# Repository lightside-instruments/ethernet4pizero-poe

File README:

The ethernet4pizero-poe project is open hardware design of a Raspbery Pi
shield that adds Ethernet over SPI connectivity with the ENC28J60 IC and
Power over Ethernet (POE) capability that can supply 2A at 5V.

The powermod directory contains design of a submodule board to handle DC-DC
conversion. The powermod submodule interface is generic and the
implementation added is based on tps54260. 

The project includes schematics and PCB
design files for KiCAD. The board can be used with
the dtoverlay=enc28j60 option added to /boot/config.txt.

The project is published by Lightside Instruments AS
under TAPR Open Hardware License. Read the LICENSE file
for details.

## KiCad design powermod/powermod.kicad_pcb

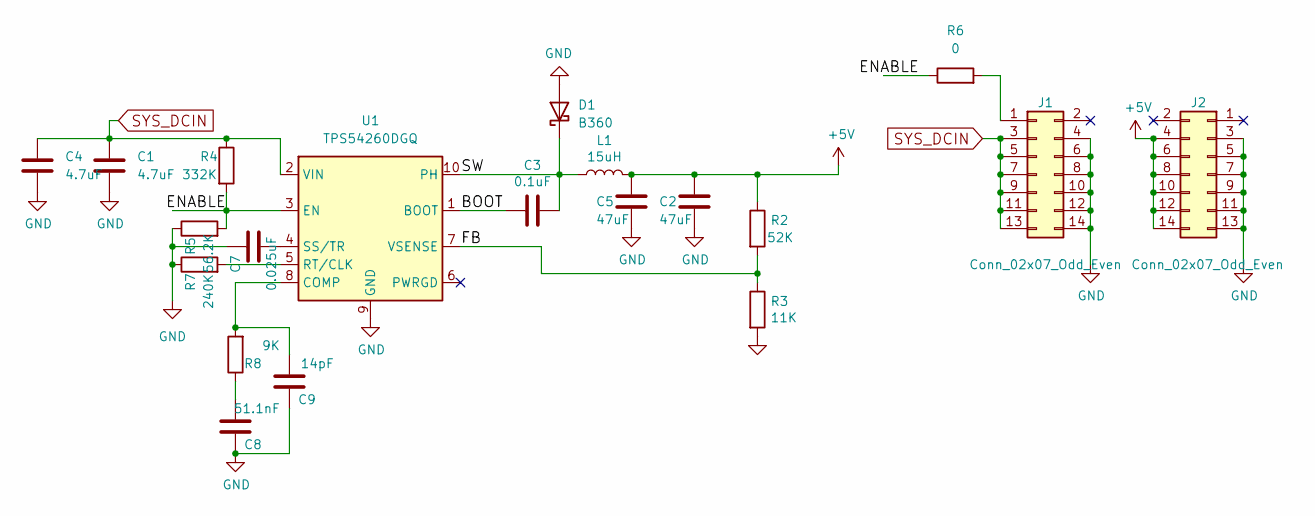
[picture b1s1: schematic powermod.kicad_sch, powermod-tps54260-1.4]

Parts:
C1, C4: 4.7uF; C_1210_3225Metric
C2, C5: 47uF; C_0805_2012Metric
C3: 0.1uF; C_0402_1005Metric
C7: 0.025uF; C_0402_1005Metric
C8: 51.1nF; C_0402_1005Metric
C9: 14pF; C_0402_1005Metric
D1: B360; D_SMC
J1, J2: Conn_02x07_Odd_Even; PinHeader_2x07_P2.00mm_Vertical_SMD
L1: 15uH; L_Taiyo-Yuden_MD-5050
R2: 52K; R_0402_1005Metric
R3: 11K; R_0402_1005Metric
R4: 332K; R_0402_1005Metric
R5: 56.2K; R_0402_1005Metric
R6: 0; R_0402_1005Metric
R7: 240K; R_0402_1005Metric
R8: 9K; R_0402_1005Metric
U1: TPS54260DGQ; MSOP-10-1EP_3x3mm_P0.5mm_EP2.2x3.1mm_Mask1.83x1.89mm_Therma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

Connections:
+5V: C2.1, C5.1, J2.4, J2.6, J2.8, J2.10, J2.12, J2.14, L1.2, R2.1
/BOOT: C3.2, U1.1 (BOOT)
/ENABLE: R4.2, R5.2, R6.1, U1.3 (EN)
/FB: R2.2, R3.1, U1.7 (VSENSE)
/SW: C3.1, D1.1 (K), L1.1, U1.10 (PH)
GND: C1.2, C2.2, C4.2, C5.2, C7.1, C8.1, C9.1, D1.2 (A), J1.4, J1.6, J1.8, J1.10, J1.12, J1.14, J2.3, J2.5, J2.7, J2.9, J2.11, J2.13, R3.2, R5.1, R7.1, U1.9 (GND), U1.11 (GND)
unnamed: C8.2, R8.1
unnamed: J1.1, R6.2
unnamed: C9.2, R8.2, U1.8 (COMP)
unnamed: R7.2, U1.5 (RT/CLK)
unnamed: C7.2, U1.4 (SS/TR)
SYS_DCIN: C1.1, C4.1, J1.3, J1.5, J1.7, J1.9, J1.11, J1.13, R4.1, U1.2 (VIN)

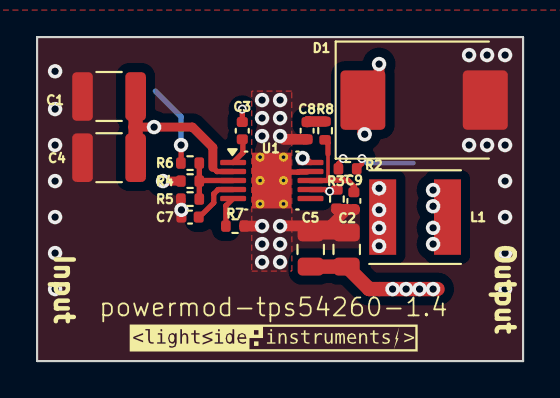
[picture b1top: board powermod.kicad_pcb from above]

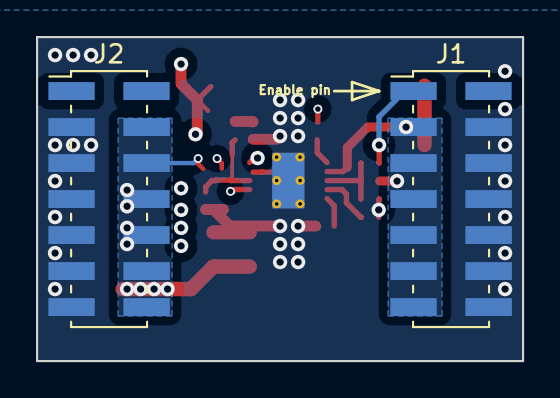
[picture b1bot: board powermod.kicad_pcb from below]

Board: 4 copper layers, 27.0 x 18.0 mm, 21 parts (2 on the bottom side), 12 nets.

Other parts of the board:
svg2mod: G***; lsi-logo-16mm

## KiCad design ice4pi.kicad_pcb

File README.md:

```
The ethernet4pizero-poe project is open hardware design of a Raspbery Pi
shield that adds Ethernet over SPI connectivity with the ENC28J60 IC and
Power over Ethernet (POE) capability that can supply 2A at 5V.

The powermod directory contains design of a submodule board to handle DC-DC
conversion. The powermod submodule interface is generic and the
implementation added is based on tps54260. 

The project includes schematics and PCB
design files for KiCAD. The board can be used with
the dtoverlay=enc28j60 option added to /boot/config.txt.

The project is published by Lightside Instruments AS
under TAPR Open Hardware License. Read the LICENSE file
for details.
```

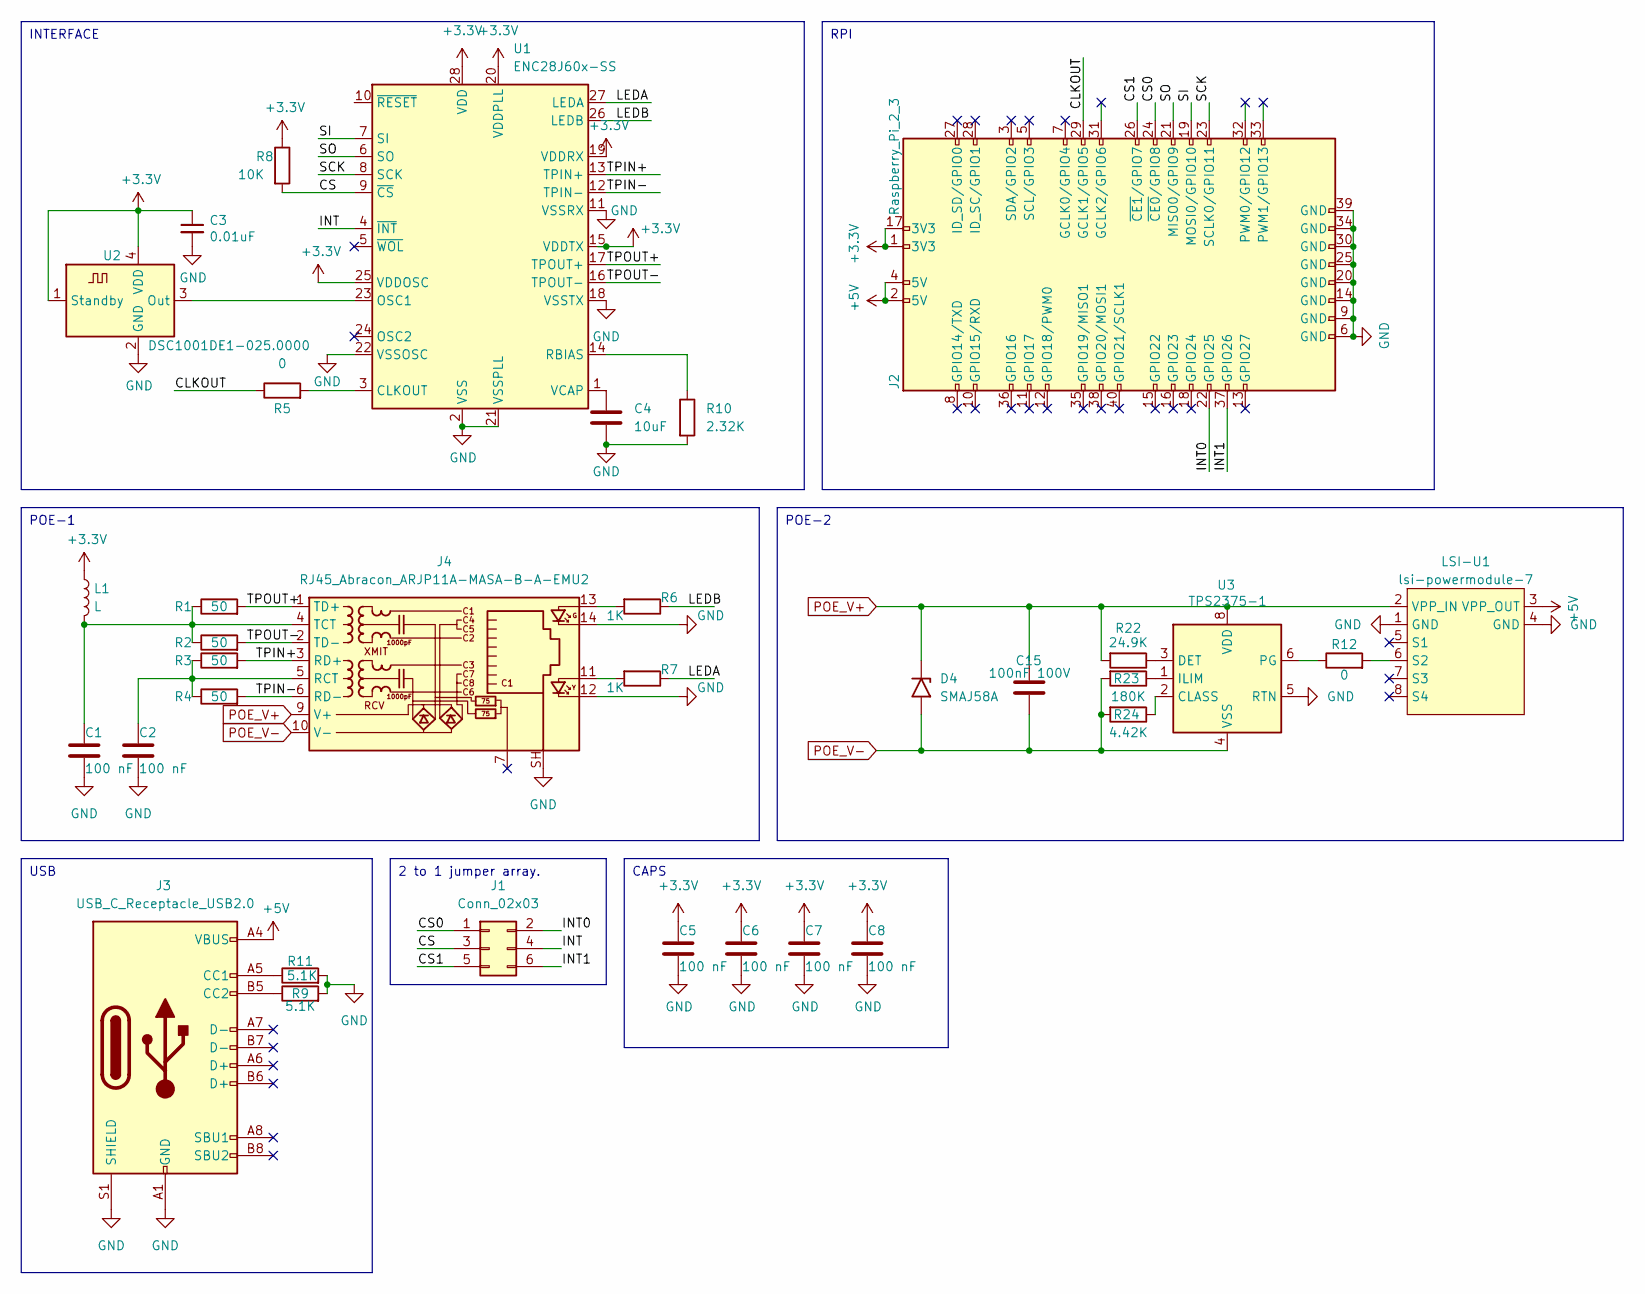
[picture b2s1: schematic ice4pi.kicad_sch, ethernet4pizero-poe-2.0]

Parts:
C1, C2, C5, C6, C7, C8: 100 nF; C_0402_1005Metric
C3: 0.01uF; C_0402_1005Metric
C4: 10uF; C_0402_1005Metric
C15: 100nF 100V; C_0402_1005Metric
D4: SMAJ58A; D_SMA
J1: Conn_02x03; PinHeader_2x03_P2.54mm_Vertical
J2: Raspberry_Pi_2_3; PinSocket_2x20_P2.54mm_Vertical_1_04mm
J3: USB_C_Receptacle_USB2.0; USB_C_Receptacle_GCT_USB4105-xx-A_16P_TopMnt_Horizontal
J4: RJ45_Abracon_ARJP11A-MASA-B-A-EMU2; RJ45_Abracon_ARJP11A-MA_Horizontal
L1: L; L_1210_3225Metric
LSI-U1: lsi-powermodule-7
R1, R2, R3, R4: 50; R_0402_1005Metric
R5, R12: 0; R_0402_1005Metric
R6, R7: 1K; R_0402_1005Metric
R8: 10K; C_0402_1005Metric
R9, R11: 5.1K; R_0402_1005Metric
R10: 2.32K; R_0402_1005Metric
R22: 24.9K; R_0402_1005Metric
R23: 180K; R_0402_1005Metric
R24: 4.42K; R_0402_1005Metric
U1: ENC28J60x-SS; SSOP-28_5.3x10.2mm_P0.65mm
U2: DSC1001DE1-025.0000; Oscillator_SMD_Abracon_ASDMB-4Pin_2.5x2.0mm
U3: TPS2375-1; TSSOP-8_4.4x3mm_P0.65mm

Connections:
+3.3V: C3.1, C5.1, C6.1, C7.1, C8.1, J2.1 (3V3), J2.17 (3V3), L1.1, R8.1, U1.15 (VDDTX), U1.19 (VDDRX), U1.20 (VDDPLL), U1.25 (VDDOSC), U1.28 (VDD), U2.1 (Standby), U2.4 (VDD)
+5V: J2.2 (5V), J2.4 (5V), J3.A4 (VBUS), J3.A9 (VBUS), J3.B4 (VBUS), J3.B9 (VBUS), LSI-U1.3 (VPP_OUT)
/CLKOUT: J2.29 (GCLK1/GPIO5), R5.1
/CS: J1.3, R8.2, U1.9 (~CS)
/CS0: J1.1, J2.24 (~CE0/GPIO8)
/CS1: J1.5, J2.26 (~CE1/GPIO7)
/INT: J1.4, U1.4 (~INT)
/INT0: J1.2, J2.22 (GPIO25)
/INT1: J1.6, J2.37 (GPIO26)
/LEDA: R7.1, U1.27 (LEDA)
/LEDB: R6.1, U1.26 (LEDB)
/SCK: J2.23 (SCLK0/GPIO11), U1.8 (SCK)
/SI: J2.19 (MOSI0/GPIO10), U1.7 (SI)
/SO: J2.21 (MISO0/GPIO9), U1.6 (SO)
/TPIN+: J4.3 (RD+), R3.2, U1.13 (TPIN+)
/TPIN-: J4.6 (RD-), R4.2, U1.12 (TPIN-)
/TPOUT+: J4.1 (TD+), R1.2, U1.17 (TPOUT+)
/TPOUT-: J4.2 (TD-), R2.2, U1.16 (TPOUT-)
GND: C1.2, C2.2, C3.2, C4.2, C5.2, C6.2, C7.2, C8.2, J2.6 (GND), J2.9 (GND), J2.14 (GND), J2.20 (GND), J2.25 (GND), J2.30 (GND), J2.34 (GND), J2.39 (GND), J3.A1 (GND), J3.A12 (GND), J3.B1 (GND), J3.B12 (GND), J3.S1 (SHIELD), J4.12, J4.14, J4.SH, LSI-U1.1 (GND), LSI-U1.4 (GND), R9.2, R10.2, R11.2, U1.2 (VSS), U1.11 (VSSRX), U1.18 (VSSTX), U1.21 (VSSPLL), U1.22 (VSSOSC), U2.2 (GND), U3.5 (RTN)
unnamed: J3.A5 (CC1), R11.1
unnamed: J3.B5 (CC2), R9.1
unnamed: J4.11, R7.2
unnamed: J4.13, R6.2
unnamed: C2.1, J4.5 (RCT), R3.1, R4.1
unnamed: C1.1, J4.4 (TCT), L1.2, R1.1, R2.1
unnamed: LSI-U1.6 (S2), R12.2
unnamed: R5.2, U1.3 (CLKOUT)
unnamed: U1.23 (OSC1), U2.3 (Out)
unnamed: R10.1, U1.14 (RBIAS)
unnamed: C4.1, U1.1 (VCAP)
unnamed: R24.1, U3.2 (CLASS)
unnamed: R22.1, U3.3 (DET)
unnamed: R23.1, U3.1 (ILIM)
unnamed: R12.1, U3.6 (PG)
POE_V+: C15.1, D4.1 (A1), J4.9 (V+), LSI-U1.2 (VPP_IN), R22.2, U3.8 (VDD)
POE_V-: C15.2, D4.2 (A2), J4.10 (V-), R23.2, R24.2, U3.4 (VSS)

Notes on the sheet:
INTERFACE
RPI
POE-2
CAPS
POE-1
USB
2 to 1 jumper array.

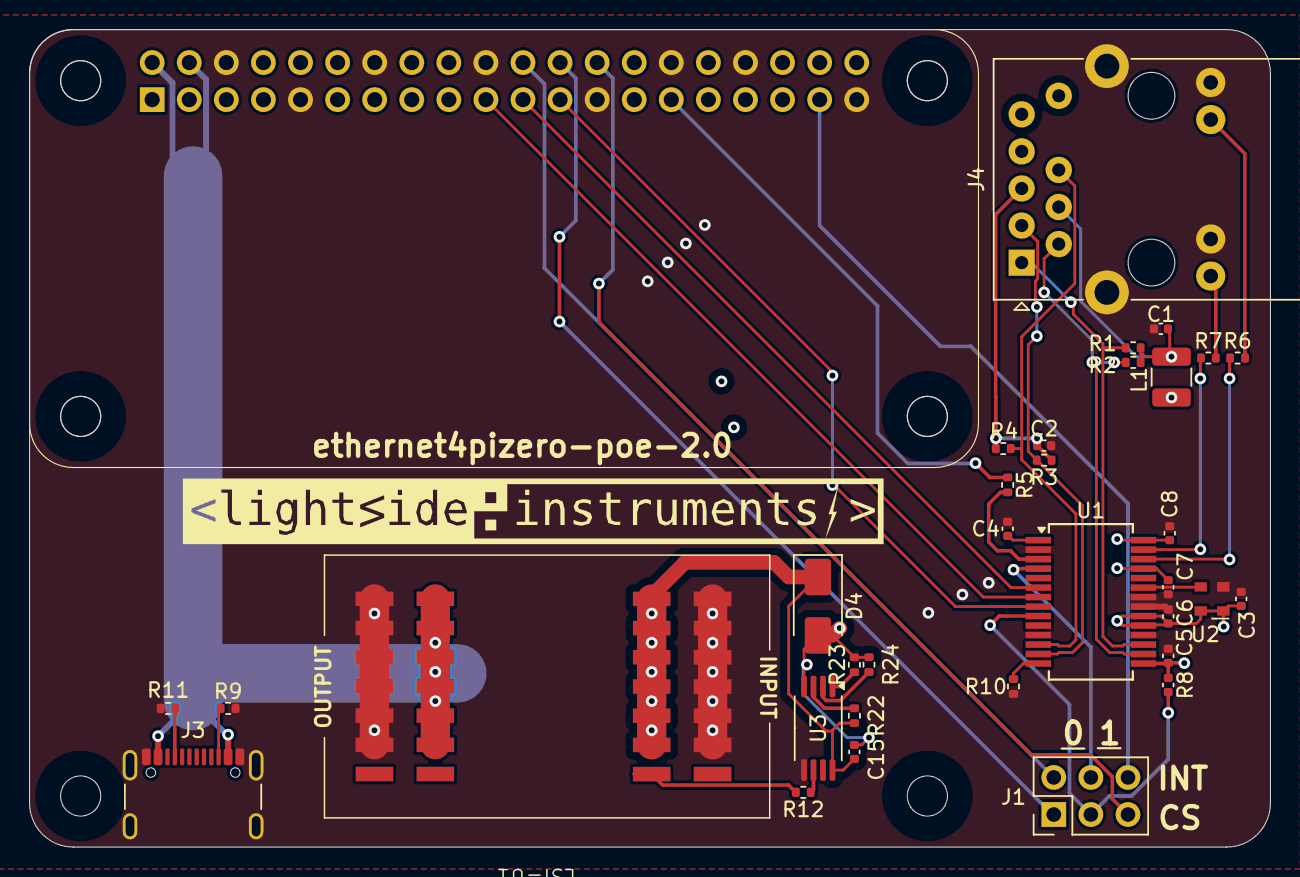
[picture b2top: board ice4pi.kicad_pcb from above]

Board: 4 copper layers, 85.0 x 56.0 mm, 35 parts (1 on the bottom side), 36 nets.

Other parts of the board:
svg2mod: G***; lsi-logo-48mm

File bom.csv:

Reference,Quantity,Identifier,footprint,Value,Tolerance,Voltage,Current,Power,PN
"C1, C2, C5, C6, C7, C8, ",6,,Capacitor_SMD:C_0402_1005Metric,100 nF,,,,,885012205037
"C3, ",1,,Capacitor_SMD:C_0402_1005Metric,0.01uF,,,,,885012205012
"C4, ",1,,Capacitor_SMD:C_0402_1005Metric,10uF,,,,,ZRB15XR61A106ME01D
"J1, ",1,,Connector_PinHeader_2.54mm:PinHeader_2x03_P2.54mm_Vertical,Conn_02x03,,,,,TSW-103-23-F-D
"J2, ",1,,ice4pi:PinSocket_2x20_P2.54mm_Vertical_1_04mm,Raspberry_Pi_2_3,,,,,SSQ-120-03-T-D
"J3, ",1,,Connector_USB:USB_C_Receptacle_GCT_885012205012P_TopMnt_Horizontal,USB_C_Receptacle_USB2.0,,,,,USB4105-GF-A 
"J4, ",1,,Connector_RJ:RJ45_Abracon_ARJP11A-MA_Horizontal,Abracon_ARJP11A-MASA-B-A-EMU2,,,,,ARJP11A-MASA-B-A-EMU2
"L1, ",1,,Inductor_SMD:L_1210_3225Metric,L,,,,,MI1210K600R-10
"R1, R2, R3, R4, ",4,,Resistor_SMD:R_0402_1005Metric,50,,,,,RC0402JR-0750RL
"R5, ",1,,Resistor_SMD:R_0402_1005Metric,0,,,,,RC0402JR-100RL
"R6, R7, ",2,,Resistor_SMD:R_0402_1005Metric,1K,,,,,ERJ-2GEJ102X 
"R8, ",1,,Capacitor_SMD:C_0402_1005Metric,10K,,,,,ERJ-2GEJ103X
"R9, ",1,,Resistor_SMD:R_0402_1005Metric,5.1K,,,,,ERJ-2RKF5101X
"R10, ",1,,Resistor_SMD:R_0402_1005Metric,2.32K,,,,,ERJ-2RKF2321X
"U1, ",1,,Package_SO:SSOP-28_5.3x10.2mm_P0.65mm,ENC28J60x-SS,,,,,ENC28J60x-SS
"U2, ",1,,Oscillator:Oscillator_SMD_Abracon_ASDMB-4Pin_2.5x2.0mm,DSC1001DE1-025.0000,,,,,DSC1001DE1-025.0000

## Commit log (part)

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2025-01-11 etherenet4pizero-poe-prerelease-2.0
2025-02-01 etherenet4pizero-poe-prerelease-2.0-1
2025-08-21 etherenet4pizero-poe-prerelease-2.0-2
2025-08-21 etherenet4pizero-poe-prerelease-2.0-3
2025-08-29 etherenet4pizero-poe-prerelease-2.0-4
